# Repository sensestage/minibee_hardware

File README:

This repository contains the Eagle design files for the Sense/Stage MiniBee (folder minibee) and a programmer (folder programmer) for the Sense/Stage MiniBee.

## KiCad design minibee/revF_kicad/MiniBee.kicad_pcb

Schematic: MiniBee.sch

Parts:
C1, C2: 10uF; RCL_C0805
C3, C4: 0.1uF; RCL_C0402
C5: 0.1uF; RCL_C0402K
COINCELL12: COINCELL; MYSHIT_KEYSTONE_BATTERY_HOLDER
F1: PTCSMD; SPARKFUN_PTC-1206
IC1: MEGA8-AI; ATMEL_TQFP32-08
JP1: MYSHIT_2X10
JP2, JP6: MYSHIT_1X02
JP3, JP4, JP5, JP7: MYSHIT_1X01
JP8, JP9, JP10, JP11: MYSHIT_PINHD-1X1; Measurement_Point_Round-SMD-Pad_Small
JP12: +; Measurement_Point_Round-SMD-Pad_Big
JP13: -; Measurement_Point_Round-SMD-Pad_Big
JST_CONNECTOR12: JST_CONNECTOR; SPARKFUN_S2B-PH
LED1: green; LED_CHIP-LED0603
LED2: red; LED_CHIP-LED0603
LED3: yellow; LED_CHIP-LED0603
LED4: blue; LED_CHIP-LED0603
R1, R2, R3, R7: 470 ohm; RCL_R0402
R4, R5: 1k ohm; RCL_R0402
R6: 10k ohm; RCL_R0402
RESONATOR12: 12MHz; SPARKFUN_RESONATOR-SMD
SW1: Switch_SPDT_x2; alps_switch
U1: ADXL345; SPARKFUN_LGA14
VREG12: V_REG_LDOSMD; SPARKFUN_SOT23-5
XB1: XBEE; MAXSTREAM_XBEE

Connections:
/A0: IC1.23 (PC0(ADC0)), JP1.20
/A1: IC1.24 (PC1(ADC1)), JP1.19
/A2: IC1.25 (PC2(ADC2)), JP1.18
/A3: IC1.26 (PC3(ADC3)), JP1.17
/A6: IC1.19 (ADC6), JP1.14
/A7: IC1.22 (ADC7), JP1.13
/ASSOC: R3.1, XB1.15 (ASSOC/AD5/DIO5)
/D2: IC1.32 (PD2(INT0)), JP1.8
/D3: IC1.1 (PD3(INT1)), JP1.5
/D4: IC1.2 (PD4(XCK/T0)), R7.1
/D5: IC1.9 (PD5(T1)), JP1.6
/D6: IC1.10 (PD6(AIN0)), JP1.7
/D7: IC1.11 (PD7(AIN1)), XB1.9 (~DTR~/SLEEP_RQ/DI8)
/D8: IC1.12 (PB0(ICP)), JP1.9
/D9: IC1.13 (PB1(OC1A)), JP1.10
/D10: IC1.14 (PB2(SS/OC1B)), JP1.11
/D11: IC1.15 (PB3(MOSI/OC2)), JP1.12, JP7.1
/DIO3: C3.1, XB1.17 (COORD_SEL/AD3/DIO3)
/N$1: IC1.7 (PB6(XTAL1/TOSC1)), RESONATOR12.1
/N$2: IC1.8 (PB7(XTAL2/TOSC2)), RESONATOR12.3
/N$3: LED1.A, R1.2
/N$4: COINCELL12.+, JP10.1, JP12.1, JST_CONNECTOR12.2, SW1.2 (B)
/N$5: IC1.16 (PB4(MISO)), JP4.1, XB1.12 (~CTS~/DIO7)
/N$6: LED2.A, R2.2
/N$7: LED3.A, R3.2
/N$8: F1.1, JP11.1, SW1.3 (C)
/N$9: C4.2, IC1.20 (AREF)
/N$10: LED4.A, R7.2
/PWM0: R2.1, XB1.6 (PWM0/RSSI)
/RST: C3.2, IC1.29 (PC6(/RESET)), JP3.1, R6.1
/RTS: IC1.17 (PB5(SCK)), JP5.1, XB1.16 (~RTS~/AD6/DIO6)
/RX: IC1.30 (PD0(RXD)), JP1.4, JP2.2, XB1.2 (DOUT)
/SCL: IC1.28 (PC5(ADC5/SCL)), JP1.15, R4.2, U1.14 (SCL)
/SDA: IC1.27 (PC4(ADC4/SDA)), JP1.16, R5.2, U1.13 (SDA)
/TX: IC1.31 (PD1(TXD)), JP1.3, JP2.1, XB1.3 (DIN/~CONFIG)
/V_IN: C1.1, F1.2, VREG12.1 (IN), VREG12.3 (EN)
GND: C1.2, C2.2, C4.1, C5.2, COINCELL12.-, IC1.3 (GND), IC1.5 (GND), IC1.21 (GND), JP1.2, JP6.1, JP13.1, JST_CONNECTOR12.1, LED1.C, LED2.C, LED3.C, LED4.C, RESONATOR12.2, U1.2 (GND), U1.4 (GND1), U1.5 (GND2), U1.10 (GND3), U1.11 (N/C), U1.12 (SDO), VREG12.2 (GND), XB1.10 (GND)
unnamed: JP8.1, U1.8 (INT1)
unnamed: JP9.1, U1.9 (INT2)
VCC: C2.1, C5.1, IC1.4 (VCC), IC1.6 (VCC), IC1.18 (AVCC), JP1.1, JP6.2, R1.1, R4.1, R5.1, R6.2, U1.1 (VDD), U1.3 (NC), U1.6 (VSS), U1.7 (CS), VREG12.5 (OUT), XB1.1 (VCC)

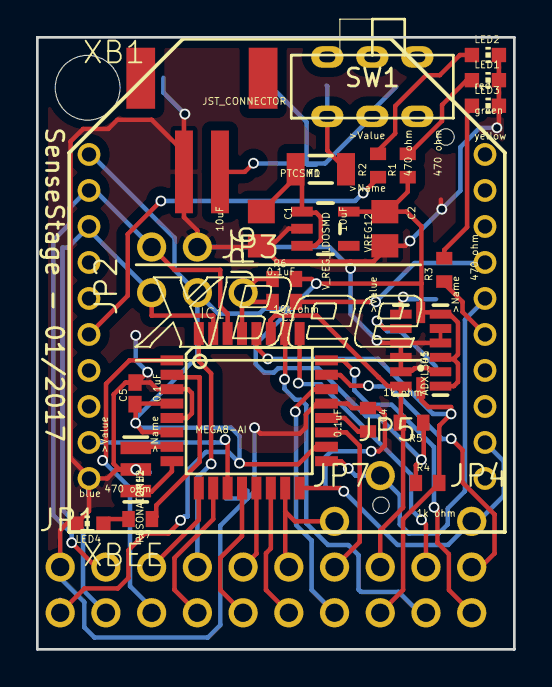
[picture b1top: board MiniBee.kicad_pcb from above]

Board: 2 copper layers, 26.5 x 34.0 mm, 39 parts (0 on the bottom side), 40 nets.

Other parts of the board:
@HOLE0: (no value)

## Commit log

2010-11-18 add the revision C eagle files
2010-11-18 added breakout pins for programmer for D11 and GND and Vcc (3v3)
2011-01-11 updates to the board - routing all the wires to the new pins
2011-01-11 fixed the font thickness and added some labels
2011-01-11 gerber files for the MiniBee
2011-01-17 i2c envir files, and drill file for MiniBee board.
2011-01-17 more directory cleanup actions.
2011-02-08 Start of a revision E. Uses SMD footprint headers and a different coincell holder. Also features an 8-pin programming header. Resulting in a bigger board, though routing is still tricky. Not finished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
2011-02-08 minor changes
2011-02-08 fix some routes
2011-04-07 switch around GND/3v3 and RX/TX so board is more compatible with revB.
2011-04-08 cleanup of some traces and vias; moved the ME led a bit.
2011-04-13 added one more via between ground planes.
2011-05-09 programmer board for MiniBee revD
2011-05-09 updates to the board with layers with the component orientation
2011-05-11 adjusted board to olimex specs, and added the design rules from them
2011-06-20 update to programmer board
2011-06-22 update to MiniBee board (show all layers), and fix BOM.
2011-08-26 updates to the programmer - still have to double check the new hole positions with XPlorer board
2012-08-14 reorganise directories
2012-08-20 add README file
2013-06-12 add revA for historical purposes
2013-07-04 raspberry pi xbee coordinator shield
2014-02-21 updates to the board based on feedback from manufacturer
2017-01-17 kicad conversion and fixes of revD board
2017-01-17 gerber files for modified revD
2017-01-17 updates to board: exchanged D2 and D7, other switch
2017-01-17 switch footprint, updated BOM
2017-01-17 updated gerbers for revision F
2017-01-17 update silkscreen to rev F
2017-01-18 rename BOM
2017-01-18 update board
2017-01-18 update BOM
2017-02-07 fix some traces (mostly the Vcc trace that was close to the edge)
2019-05-11 additional files for rev F
